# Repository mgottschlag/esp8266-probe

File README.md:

# esp8266-probe

This repository contains a PCB design for a WIFI JTAG probe using the ESP-12
ESP8266 module. The probe is designed to be compatible with
[blackmagic-espidf](https://github.com/walmis/blackmagic-espidf). The JTAG
signals (+UART) are connected as follows to ESP8266 GPIOs:

| JTAG Signal | GPIO |
| ----------- | ---- |
| TXD         | 1    |
| RXD         | 3    |
| TMS/SWDIO   | 4    |
| TCK/SWCLK   | 5    |
| SRST        | 12   |
| TDI         | 13   |
| TDO         | 14   |

In addition, the 10-pin connector provides 5V and 3.3V supplies. The PCB is
provided with power via USB and 3.3V is provided by a cheap 1117 linear
regulator.

## License

The design is licensed under the [CERN Open Hardware Licence Version 2 - Permissive](cern-ohl_p_v2.txt).

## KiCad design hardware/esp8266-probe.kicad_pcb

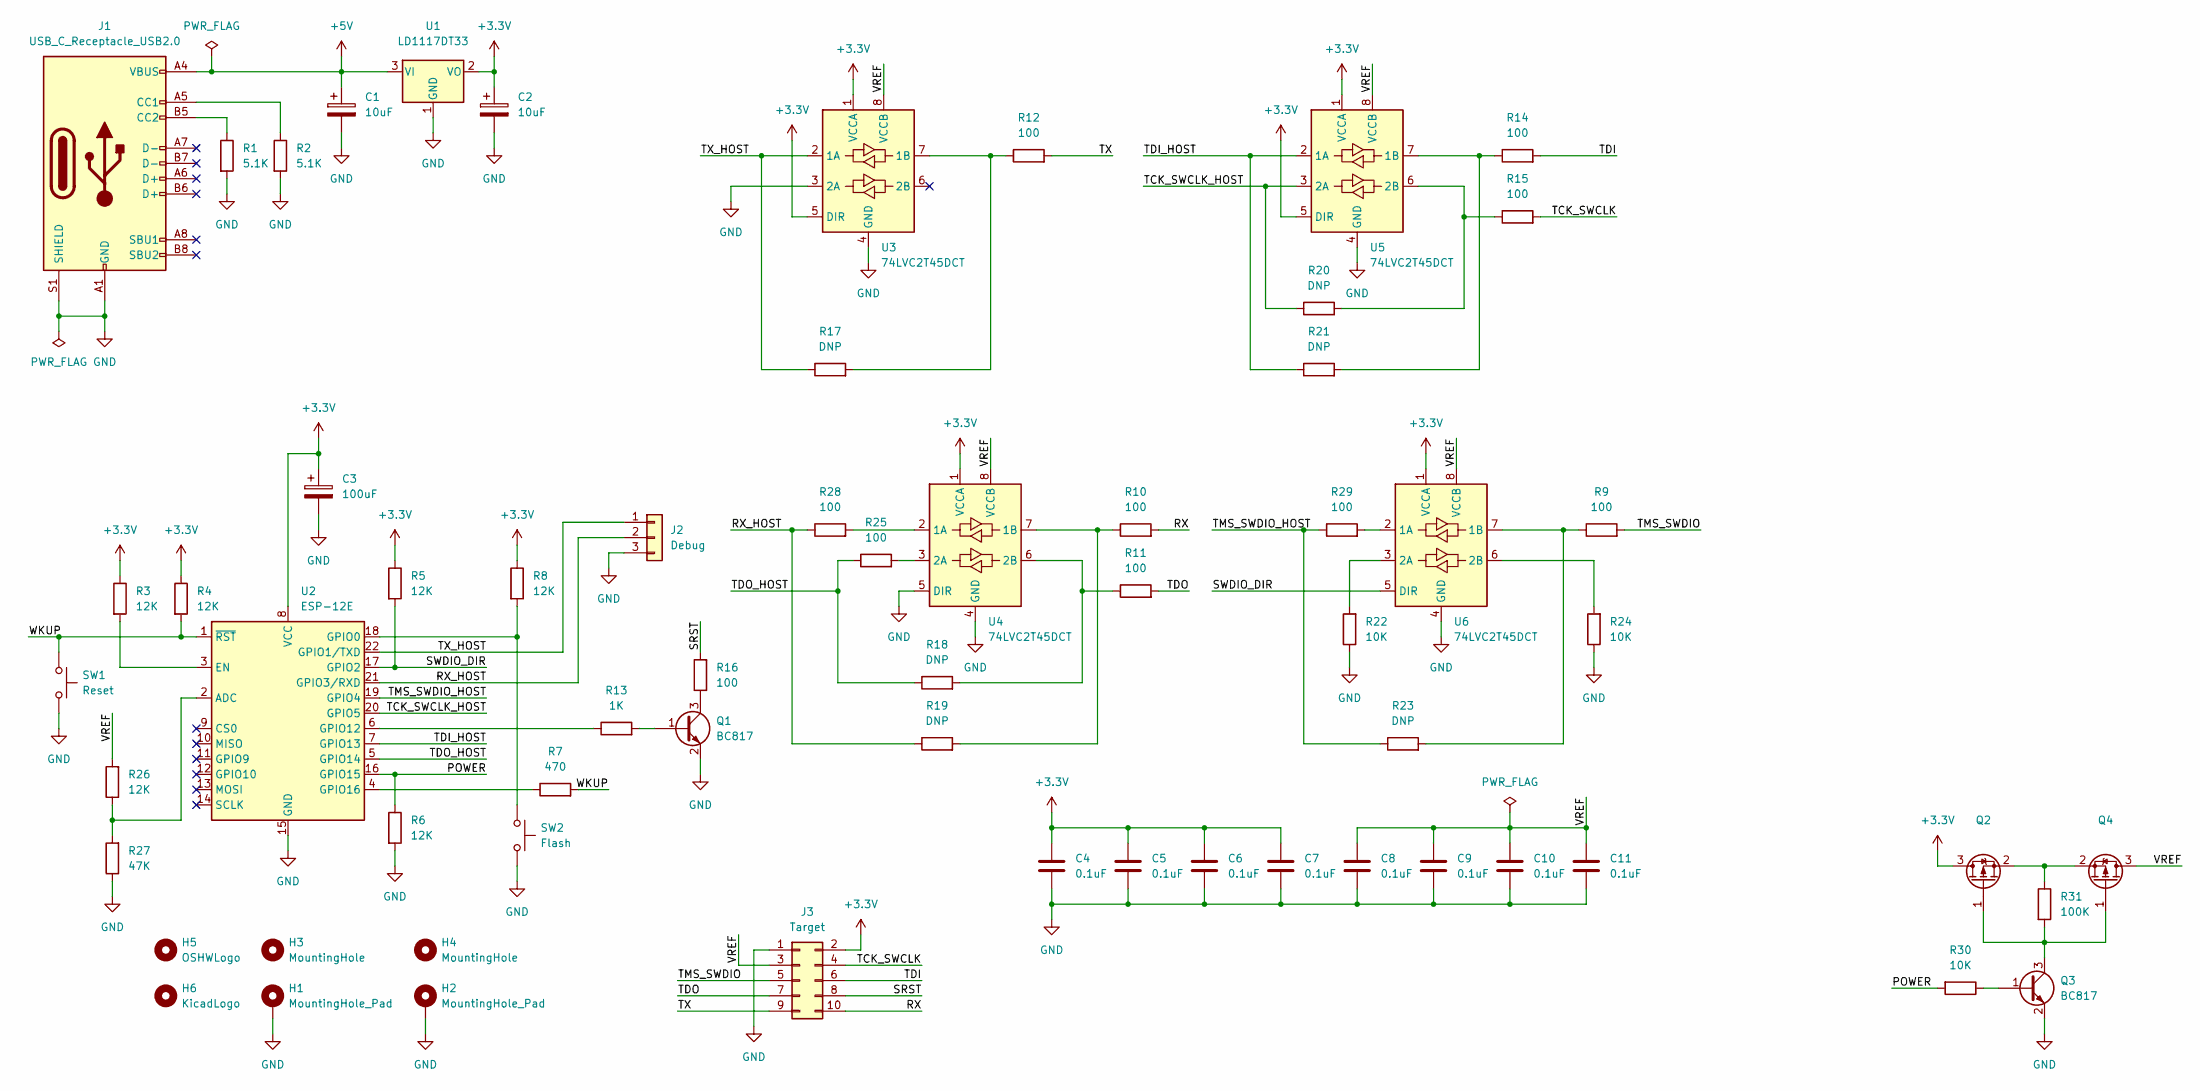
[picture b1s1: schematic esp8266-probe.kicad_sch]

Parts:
C1, C2: 10uF; CP_EIA-6032-20_AVX-F_Pad2.25x2.35mm_HandSolder
C3: 100uF; CP_Radial_D6.3mm_P2.50mm
C4, C5, C6, C7, C8, C9, C10, C11: 0.1uF; C_0603_1608Metric
H1, H2: MountingHole_Pad; MountingHole_3.2mm_M3_Pad
H3, H4: MountingHole; MountingHole_3.2mm_M3
H5: OSHWLogo; OSHW-Logo_5.7x6mm_SilkScreen
H6: KicadLogo; KiCad-Logo2_5mm_SilkScreen
J1: USB_C_Receptacle_USB2.0; USB_C_Receptacle_HRO_TYPE-C-31-M-12
J2: Debug; PinHeader_1x03_P2.54mm_Vertical
J3: Target; IDC-Header_2x05_P2.54mm_Vertical
Q1, Q3: BC817; SOT-23
Q2: (no value)
Q4: SOT-23
R1, R2: 5.1K; R_0603_1608Metric
R3, R4, R5, R6, R8, R26: 12K; R_0603_1608Metric
R7: 470; R_0603_1608Metric
R9, R10, R11, R12, R14, R15, R16, R25, R28, R29: 100; R_0603_1608Metric
R13: 1K; R_0603_1608Metric
R17, R18, R19, R20, R21, R23: DNP; R_0603_1608Metric
R22, R24, R30: 10K; R_0603_1608Metric
R27: 47K; R_0603_1608Metric
R31: 100K; R_0603_1608Metric
SW1: Reset; SW_SPST_PTS810
SW2: Flash; SW_SPST_PTS810
U1: LD1117DT33; TO-252-2
U2: ESP-12E
U3, U4, U5, U6: 74LVC2T45DCT; VSSOP-8_3.0x3.0mm_P0.65mm

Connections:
+3V3: C2.1, C3.1, C4.1, C5.1, C6.1, C7.1, J3.2, Q2.3 (D), R3.1, R4.1, R5.1, R8.1, U1.2 (VO), U2.8 (VCC), U3.1 (VCCA), U3.5 (DIR), U4.1 (VCCA), U5.1 (VCCA), U5.5 (DIR), U6.1 (VCCA)
+5V: C1.1, J1.A4 (VBUS), J1.A9 (VBUS), J1.B4 (VBUS), J1.B9 (VBUS), U1.3 (VI)
/POWER: R6.1, R30.2, U2.16 (GPIO15)
/RX: J3.10, R10.2
/RX_HOST: J2.2, R19.1, R28.1, U2.21 (GPIO3/RXD)
/SRST: J3.8, R16.2
/SWDIO_DIR: R5.2, U2.17 (GPIO2), U6.5 (DIR)
/TCK_SWCLK: J3.4, R15.2
/TCK_SWCLK_HOST: R20.1, U2.20 (GPIO5), U5.3 (2A)
/TDI: J3.6, R14.2
/TDI_HOST: R21.1, U2.7 (GPIO13), U5.2 (1A)
/TDO: J3.7, R11.2
/TDO_HOST: R18.1, R25.1, U2.5 (GPIO14)
/TMS_SWDIO: J3.5, R9.2
/TMS_SWDIO_HOST: R23.1, R29.1, U2.19 (GPIO4)
/TX: J3.9, R12.2
/TX_HOST: J2.1, R17.1, U2.22 (GPIO1/TXD), U3.2 (1A)
/VREF: C8.1, C9.1, C10.1, C11.1, J3.3, Q4.3 (D), R26.2, U3.8 (VCCB), U4.8 (VCCB), U5.8 (VCCB), U6.8 (VCCB)
/WKUP: R4.2, R7.2, SW1.1, U2.1 (~RST)
GND: C1.2, C2.2, C3.2, C4.2, C5.2, C6.2, C7.2, C8.2, C9.2, C10.2, C11.2, H1.1, H2.1, J1.A1 (GND), J1.A12 (GND), J1.B1 (GND), J1.B12 (GND), J1.S1 (SHIELD), J2.3, J3.1, Q1.2 (E), Q3.2 (E), R1.2, R2.2, R6.2, R22.1, R24.1, R27.1, SW1.2, SW2.2, U1.1 (GND), U2.15 (GND), U3.3 (2A), U3.4 (GND), U4.4 (GND), U4.5 (DIR), U5.4 (GND), U6.4 (GND)
unnamed: J1.A5 (CC1), R2.1
unnamed: J1.B5 (CC2), R1.1
unnamed: Q1.1 (B), R13.2
unnamed: Q1.3 (C), R16.1
unnamed: Q2.1 (G), Q3.3 (C), Q4.1 (G), R31.2
unnamed: Q2.2 (S), Q4.2 (S), R31.1
unnamed: Q3.1 (B), R30.1
unnamed: R3.2, U2.3 (EN)
unnamed: R7.1, U2.4 (GPIO16)
unnamed: R8.2, SW2.1, U2.18 (GPIO0)
unnamed: R10.1, R19.2, U4.7 (1B)
unnamed: R11.1, R18.2, U4.6 (2B)
unnamed: R12.1, R17.2, U3.7 (1B)
unnamed: R13.1, U2.6 (GPIO12)
unnamed: R14.1, R21.2, U5.7 (1B)
unnamed: R15.1, R20.2, U5.6 (2B)
unnamed: R22.2, U6.3 (2A)
unnamed: R9.1, R23.2, U6.7 (1B)
unnamed: R24.2, U6.6 (2B)
unnamed: R25.2, U4.3 (2A)
unnamed: R26.1, R27.2, U2.2 (ADC)
unnamed: R28.2, U4.2 (1A)
unnamed: R29.2, U6.2 (1A)

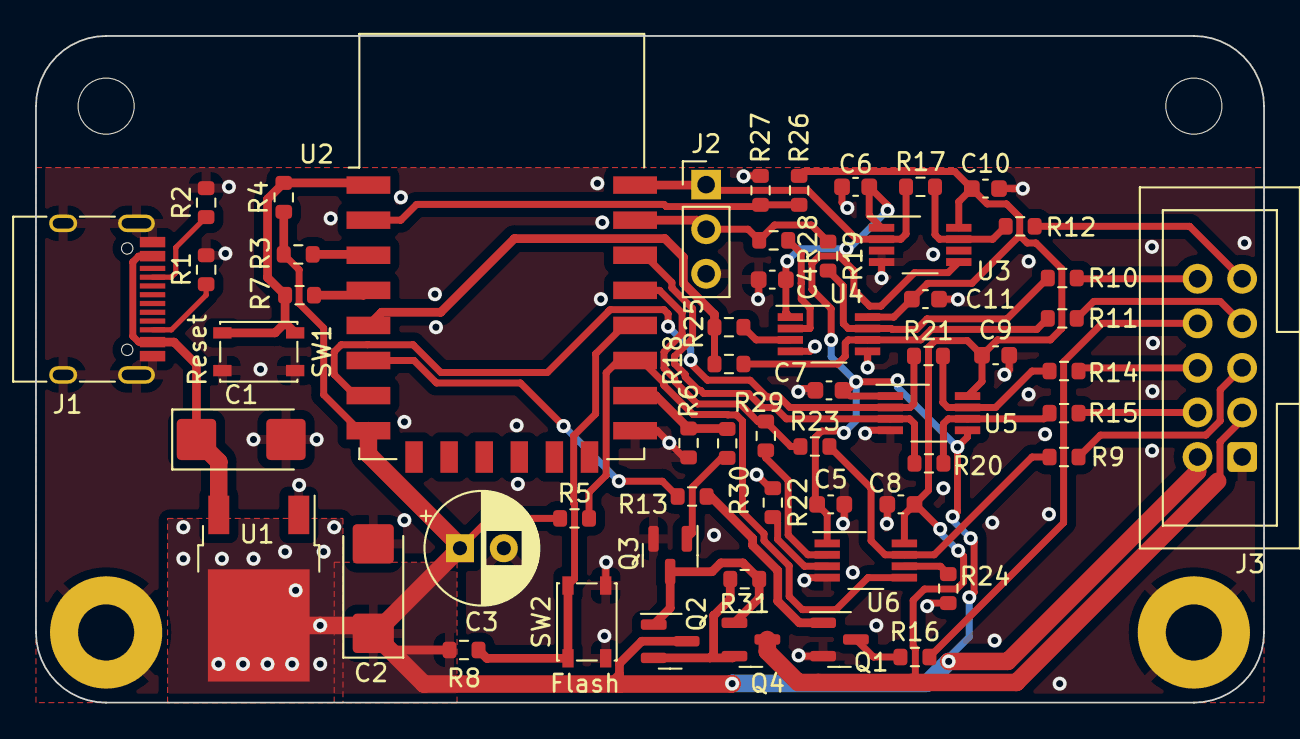
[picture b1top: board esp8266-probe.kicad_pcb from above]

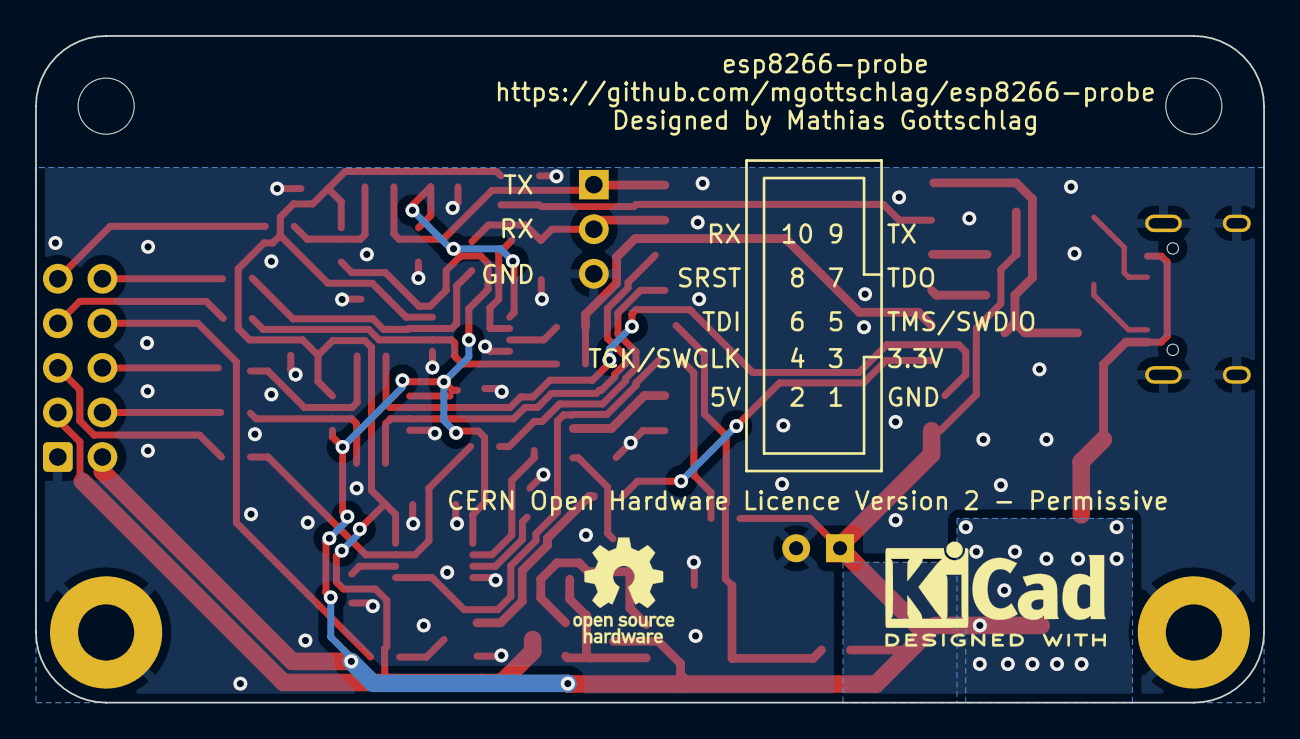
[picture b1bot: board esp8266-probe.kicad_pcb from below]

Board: 2 copper layers, 70.0 x 38.0 mm, 63 parts (2 on the bottom side), 43 nets.

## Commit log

2022-04-10 Initial import of the PCB.
2022-04-10 Add a README file and the license terms.
2022-04-10 Improve thermal design around the linear regulator.
2022-04-10 Add more ground vias.
2022-04-10 Add DebugEdge git submodule (for the KiCAD symbol/footprint).
2022-04-18 Added level shifters and power to the PCB.
